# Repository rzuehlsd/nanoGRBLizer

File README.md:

# nanoGRBLizer
nanoGRBLizer is a GRBL 1.1 based Arduino Nano controller for Stepcraft SC420 D2 milling machine.
The design is based on the well known GRBLizer controller specifically designed for the Stepcraft mills by Rogier Lodewijks (see https://github.com/eflukx/Stepcraft-GRBLizer). 
The nanoGRBLizer controller uses the open source GRBL1.1h software (https://github.com/gnea/grbl/wiki) and allows in combination with a GRBL code sender (eg. UltimateCNC or UGS) controll of all 3 axes and the spindle of the stepcraft mill. A probe length sens input is also available. 

The functionality of the nanoGRBLizer compared to the original GRBLizer lacks the connections to controll a 4th axis and additional relais. Dimensions and functionalty of the nanoGRBLizer PCB allow for a 1:1 replacement of the WinPCNC USB controller of the Stepcraft mills, which is often used for hobby purposes.

I first tried the original GRBLizer and ordered a PCB by PCBWay but realized that getting the required parts was problematic and costly. I therefore reduced the original design to the functionalities I really needed and had a specific focus on simplicity and cost. As a result I designed the nanoGRBLizer around a Arduino Nano bord which reduced the complexity a lot and was also very cost efficient. 

This repository holds the KiCAD files to replicate the nanoGRBLizer and gives hints for implementation, configuration and initial operation of the nanoGRBLizer.

## PCB Assembly
There are some caveeats which have to be respected during assembly of the PCB due to the space constraints of the Stepcraft mill.
- First the 6 pin ISP header of the Arduino Nano has to be shorted by about 3mm. Alternatively you have to unsolder the header or insolate it, as the metal shield of the Stepcraft driver board might shorten the pins.
- Directly solder the Arduino Nano on the PCB. Do **not use a socket** as the PCB might not fit into the available space and the USB socket might not be usable.

## Installation of GRBL1.1 firmware
- Download the current version of the GRBL 1.1 software from here: https://github.com/gnea/grbl
- Install the grbl lib according to your Arduino IDE
- Implement the changes to the files cpu_map.h and config.h as described in the next section
- Compile the grbl_uload.ino script from the grbl examples and download to your Nano

## Configuration of Controller
I implemented the grbl settings as described by Rogier in his readme. They did not quite worked for me, but were a very good starting point. 
As I wanted to use the HF500 spindle with my SC420 mill I had to figure out how to get the spindle enable signal on A3 working.
I changed the config.h, the cpu_map.h and the defaults.h file to reflect the changes needed by my configuration. To avoid chnaging configuration settings inside the default configuration for Atmega328 microprocessor I decided to redefine required symbols inside a conditional block directly below the default settings. This redefinitions are guarded by a `#ifdef NANO_GRBLIZER ... #endif` bracket. The symbol NANO_GRBLIZER was then definded in config.h as shown below:
```
// Define CPU pin map and default settings.
// NOTE: OEMs can avoid the need to maintain/update the defaults.h and cpu_map.h files and use only
// one configuration file by placing their specific defaults and pin map at the bottom of this file.
// If doing so, simply comment out these two defines and see instructions below.
#define DEFAULTS_GENERIC
#define CPU_MAP_ATMEGA328P // Arduino Uno CPU
#define NANO_GRBLIZER       // triggers redefinitions in config.h, cpu_map.h and defaults.h for nanoGRBLizer
```
Now add the following code snippet to config.h at the **end of the file**:

```
#ifdef NANO_GRBLIZER

// Paste config redefinitions for nanoGRBLIzer  here:

// do not raise alarm to force initial homing at startup
#undef HOMING_INIT_LOCK // Comment to disable

// Since all limit switches end up being shared on one pin, 
// we can only home one direction at a time.
#define HOMING_CYCLE_0 (1<<Z_AXIS)  // REQUIRED: First move Z to clear workspace.
#define HOMING_CYCLE_1 (1<<Y_AXIS)  // OPTIONAL: Then move X,Y at the same time.
#define HOMING_CYCLE_2 (1<<X_AXIS)  // OPTIONAL: Uncomment and add axes mask to enable

// The stop output of the Stepcraft board is inverted to what GRBL expects.
// However you simply can't swap the switch because the driver board will also
// disable the motors so nothing will move.
#define INVERT_CONTROL_PIN_MASK (1<<CONTROL_RESET_BIT) // Default disabled.

// use safety door open event to stop mill and spindle with emergency stop switch
#define ENABLE_SAFETY_DOOR_INPUT_PIN // Default disabled. Uncomment to enable.

// Allows operation of Stepcraft HF500 spindle via grbl
// Activates definition of spindle on/off signal
#define USE_SPINDLE_DIR_AS_ENABLE_PIN

#endif
```

Now lets change the cpu_map.h file for nanGRBLizer. Past the following code directly below the CPU_MAP_ATMEGA328P definitions into the file.

```
#ifdef NANO_GRBLIZER

// Paste cpu_map.h redefinitions for nanoGRBLizer here.

/* Additional or changed Grbl cpu mappings for nanoGRBLizer v01 with Arduini Nano
   Mill:      Stepcraft sc420 D2
   Spindle:   Stepcraft HF500
*/

// The Stepcraft has all limits on one pin.
#define X_LIMIT_BIT    1  // Uno Digital Pin 9
#define Y_LIMIT_BIT    1  // Uno Digital Pin 9
#define Z_LIMIT_BIT    1  // Uno Digital Pin 9

// redefinition of coolant enable port to save A3 for spindle
#define COOLANT_FLOOD_BIT   6  // Uno Analog Pin 3

// redefinition of safty door bit to be shared with CONTROL_RESET_BIT
// hope this will shutsdown spindle and mill when triggered by E-Stop 
#define CONTROL_SAFETY_DOOR_BIT   0

// redefinition of spindle enable port 
// needs definition of USE_SPINDLE_DIR_AS_ENABLE_PIN in config.h 
// to allow for seperate spindle on/off signal via A3
#define SPINDLE_ENABLE_DDR    DDRC
#define SPINDLE_ENABLE_PORT   PORTC
#define SPINDLE_ENABLE_BIT    3  // Uno Analog Pin 3

#endif //  NANO_GRBLIZER
```

Add the changes to the default parameter definition. Past the following section directly below the `DEFAULTS_GENERIC` block.

```
#ifdef NANO_GRBLIZER

  // Paste changes to generic default settings for nanoGRBLizer with sc420 and HF500 here.

  // My old version of Stepcraft sc420 has spindles with 2mm travel per revolution!
  // At 400 half steps per revolution this leads to 200.000 half steps per millimeter
  // whereas the newer versions have spindles with 3mm travel per revolution, hence
  // 133.333 half steps per mm travel!

  #define DEFAULT_X_STEPS_PER_MM 200.000		// standard will be 133.333
  #define DEFAULT_Y_STEPS_PER_MM 200.000		// standard will be 133.333
  #define DEFAULT_Z_STEPS_PER_MM 200.000		// standard will be 133.333
  #define DEFAULT_X_MAX_RATE 800.0 // mm/min
  #define DEFAULT_Y_MAX_RATE 800.0 // mm/min
  #define DEFAULT_Z_MAX_RATE 800.0 // mm/min
  #define DEFAULT_X_MAX_TRAVEL 300.0 // mm NOTE: Must be a positive value.
  #define DEFAULT_Y_MAX_TRAVEL 420.0 // mm NOTE: Must be a positive value.
  #define DEFAULT_Z_MAX_TRAVEL 80.0 // mm NOTE: Must be a positive value.
  #define DEFAULT_SPINDLE_RPM_MAX 20000.0 // rpm
  #define DEFAULT_SPINDLE_RPM_MIN 3000.0 // rpm
  #define DEFAULT_STEP_PULSE_MICROSECONDS 50
  #define DEFAULT_STEPPER_IDLE_LOCK_TIME 100 // msec (0-254, 255 keeps steppers enabled)
  #define DEFAULT_INVERT_ST_ENABLE 1 // false
  #define DEFAULT_INVERT_LIMIT_PINS 1 // false
  #define DEFAULT_SOFT_LIMIT_ENABLE 0 // false
  #define DEFAULT_HARD_LIMIT_ENABLE 1  // false
  #define DEFAULT_INVERT_PROBE_PIN 0 // false
  #define DEFAULT_HOMING_ENABLE 1  // false
  #define DEFAULT_HOMING_DIR_MASK 1 // move x to left to find limit switch
  #define DEFAULT_HOMING_FEED_RATE 120.0 // mm/min
  #define DEFAULT_HOMING_SEEK_RATE 900.0 // mm/min
  #define DEFAULT_HOMING_DEBOUNCE_DELAY 250 // msec (0-65k)
  #define DEFAULT_HOMING_PULLOFF 1.0 // mm

#endif
```

## Initial Operation with UltimateCNC and nanoGRBLizer V1.0
I used UltimateCNC on Linux as a gcode sender and after initial connection to the nanoGRBLizer a error alarm showed up, which confused me a lot. After a few hours of debugging and head scratching I found the solution in the config.h file of the grbl library. I just disabled the HOMING_INIT_LOCK and could proceed. Homing and moving of all axes was fine, but I had a problem with the z-probing. I connected a simple probe at the probe connector of the nanGRBLizer and tried probing. I had to hit the stop switch as the bit did not stop at contact with my metal sheet. 

Measurements showed that the voltage between both pins of the probe dropped from about 5V to OV but the probe event was not triggered. Testing outside the SC420 showed normal behaviour, eg. a probe event was recognized without problems. So the problem has to be the combination of nanoGRBLizer and SC420. After I connected the probe directly to the probe connector on the stepcraft mainboard everything worked as expected! Well now I understand the optional jumper to break the connection between A5 and SC_Length in the original GRBLizer schematic.

There was just one additional change I had to make to the UltimateCNC default probe macro. The probe connected to the metal sheet and immediatldiatly raised an alarm. A closer look at the probe macro showed that after initial contact an additional G38.2 command was issued without raising the spindle.
I changed that to `G38.2 Z-50 F50; G92 Z0; G0 Z10` as a first fix and all was fine.

Further testing showed that all 3 axes did not travel the required distances. After some test and head scratching I figured out (sometimes its worth looking into the manual) that my early type of SC420 has spindles with 2mm travel distance per revolution and 200 steps per revolution stepper motors. As the Stepcraft drivers work in half step mode we have 400 half steps per revolution. After adjusting the (half) steps per mm travel to 200.000 for all axes ($100, $101 and $102) everything worked as expected.

So if you try to use this controller I hope the information above will help you. Have fun!

## IMPORTANT NOTE  - Changes to nanoGRBLizer Rev 1.1

When I tried to use AutoLevelling in UGS/UltimatCNC I discovered a very strange behavior. After initial x axis zero AutoLevellimng could bestartet but stopped at firs probe position with an error (incompatible initial state for probing). After some tests I found the reason to be the probe connected to the Stepcraft mainboard.
After I interrupted the connection to  J1 pin 10 (Stepcraft probe sense connection) and connected the probe to J1 on the nanoGRBLizer controller everything worked as expected.

These changes to the schematic and the board layout are reflected in the nanoGRBLizer Rev 1.1

In Addition I included the files for grbl V1.1h with all SC 420 D2 related changes to the config.g, cpu_map.h and defaults.h files. So just compile and upload grblUpload.ino and you are done. All relevant settings for Stepcraft SC 420 D2 are included in the code.

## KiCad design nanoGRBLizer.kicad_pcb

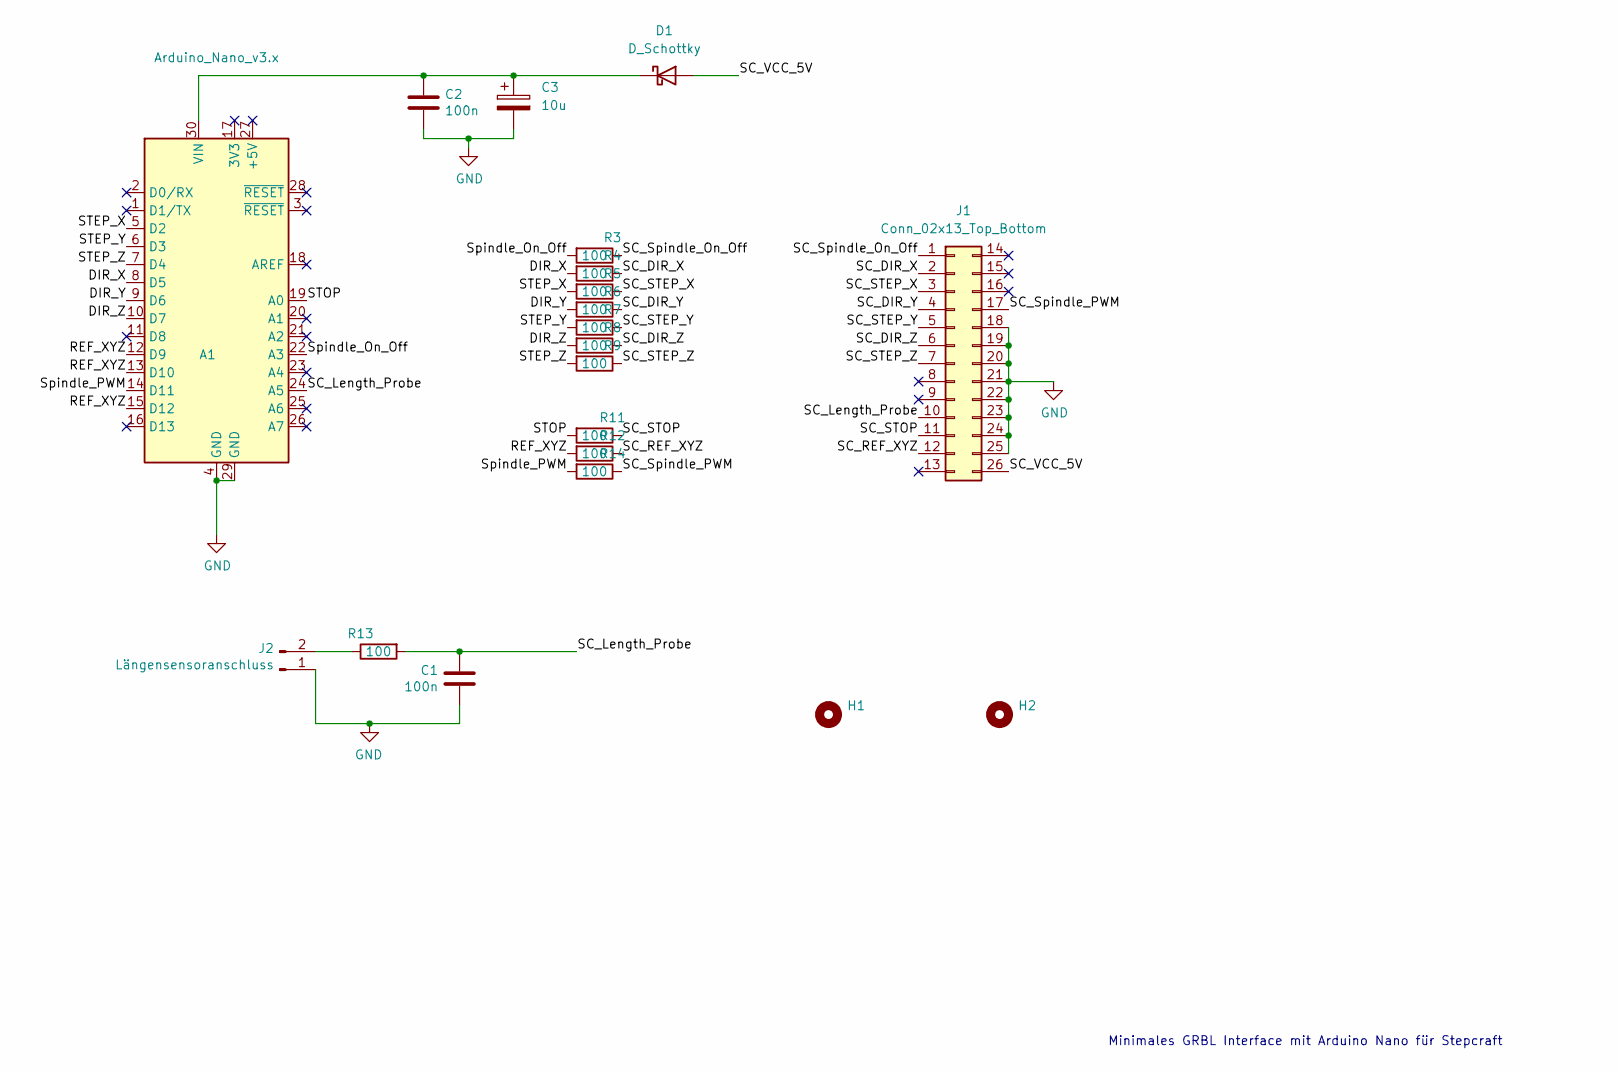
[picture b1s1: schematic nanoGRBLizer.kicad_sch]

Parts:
A1: Arduino_Nano_v3.x; Arduino_Nano
C1, C2: 100n; C_Axial_L3.8mm_D2.6mm_P7.50mm_Horizontal
C3: 10u; CP_Radial_D8.0mm_P2.50mm
D1: D_Schottky; D_DO-15_P10.16mm_Horizontal
H1, H2: MountingHole; MountingHole_3.2mm_M3
J1: Conn_02x13_Top_Bottom; PinHeader_2x13_P2.54mm_Horizontal_top_bootom
J2: Längensensoranschluss; Molex_SL_171971-0002_1x02_P2.54mm_Vertical
R3, R4, R5, R6, R7, R8, R9, R11, R12, R13, R14: 100; R_Axial_DIN0207_L6.3mm_D2.5mm_P10.16mm_Horizontal

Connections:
/DIR_X: A1.8 (D5), R4.2
/DIR_Y: A1.9 (D6), R6.2
/DIR_Z: A1.10 (D7), R8.2
/REF_XYZ: A1.12 (D9), A1.13 (D10), A1.15 (D12), R12.2
/SC_DIR_X: J1.2, R4.1
/SC_DIR_Y: J1.4, R6.1
/SC_DIR_Z: J1.6, R8.1
/SC_Length_Probe: A1.24 (A5), C1.1, J1.10, R13.2
/SC_REF_XYZ: J1.12, R12.1
/SC_STEP_X: J1.3, R5.1
/SC_STEP_Y: J1.5, R7.1
/SC_STEP_Z: J1.7, R9.1
/SC_STOP: J1.11, R11.1
/SC_Spindle_On_Off: J1.1, R3.1
/SC_Spindle_PWM: J1.17, R14.1
/SC_VCC_5V: D1.2 (A), J1.26
/STEP_X: A1.5 (D2), R5.2
/STEP_Y: A1.6 (D3), R7.2
/STEP_Z: A1.7 (D4), R9.2
/STOP: A1.19 (A0), R11.2
/Spindle_On_Off: A1.22 (A3), R3.2
/Spindle_PWM: A1.14 (D11), R14.2
GND: A1.4 (GND), A1.29 (GND), C1.2, C2.2, C3.2, J1.18, J1.19, J1.20, J1.21, J1.22, J1.23, J1.24, J1.25, J2.1
unnamed: A1.30 (VIN), C2.1, C3.1, D1.1 (K)
unnamed: J2.2, R13.1

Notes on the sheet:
Minimales GRBL Interface mit Arduino Nano für Stepcraft

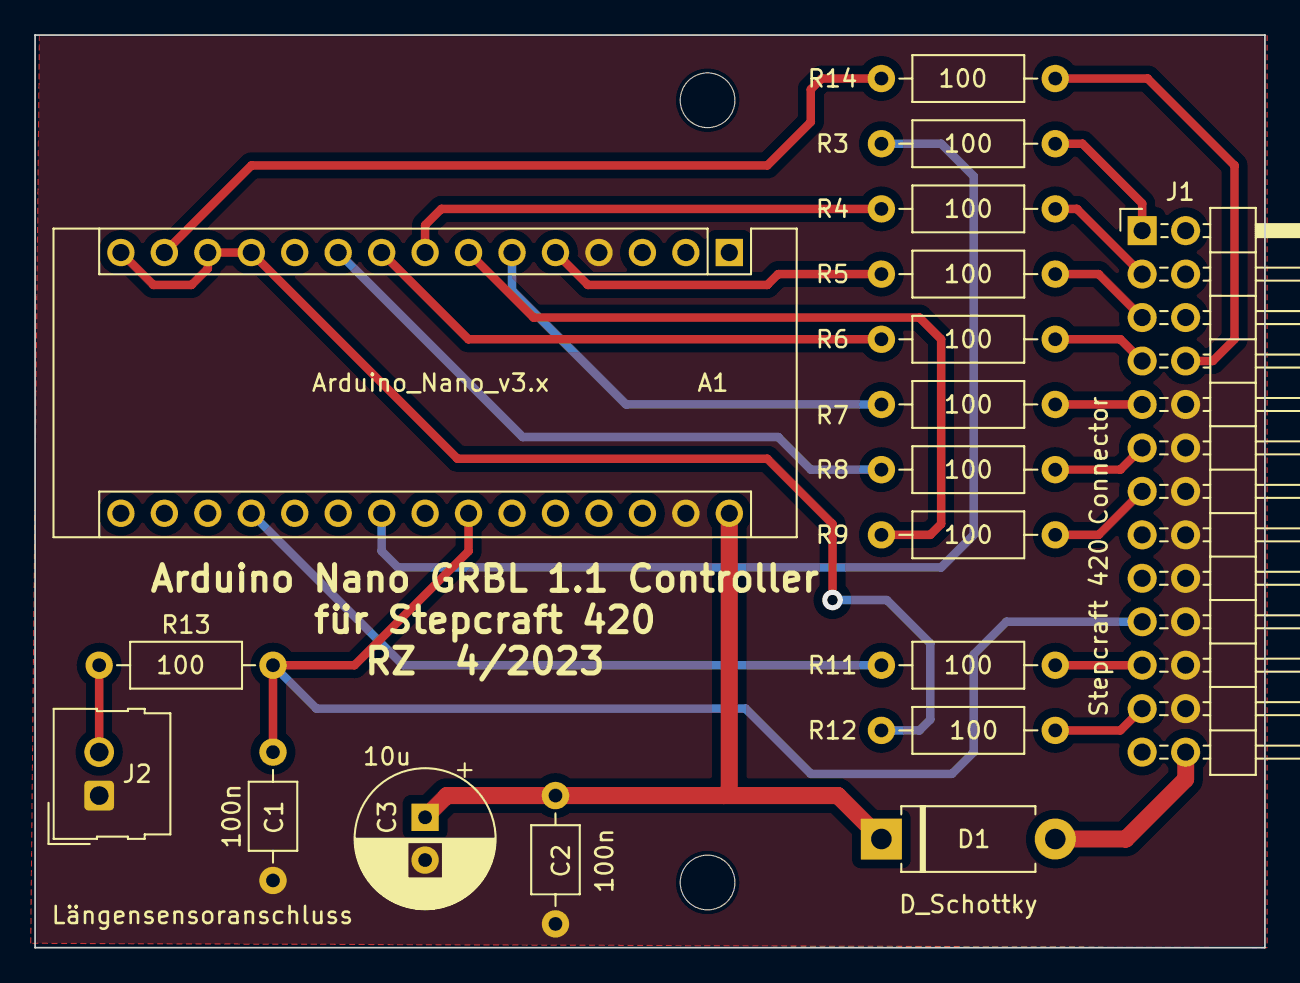
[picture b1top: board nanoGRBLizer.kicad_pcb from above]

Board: 2 copper layers, 71.9 x 53.3 mm, 20 parts (0 on the bottom side), 25 nets.

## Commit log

2023-06-20 Initial
2023-06-20 Design Information (German)
2023-06-20 Design description (German)
2023-06-20 nanoGRBLizer_schematic.pdf
2023-07-11 Add files via upload
    Changes to Dokumentation due to different settings for spindle travel per revolution
2023-07-11 Add files via upload
    Changes to GRBL parameters for $100, $101 and $102
2023-07-11 Update README.md
    Update
2024-01-15 Update README.md
    Infos for Rev 1.1
